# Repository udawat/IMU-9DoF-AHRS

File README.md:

IMU-9DoF-AHRS
=============

Explore Labs' 9 DoF IMU with Invensense's MPU-9150, Freescale Semiconductor's Pressure Sensor MPL3115A2 and Measurement Specialties' Humidity Sensor HTU21D and an optional GPS connector.

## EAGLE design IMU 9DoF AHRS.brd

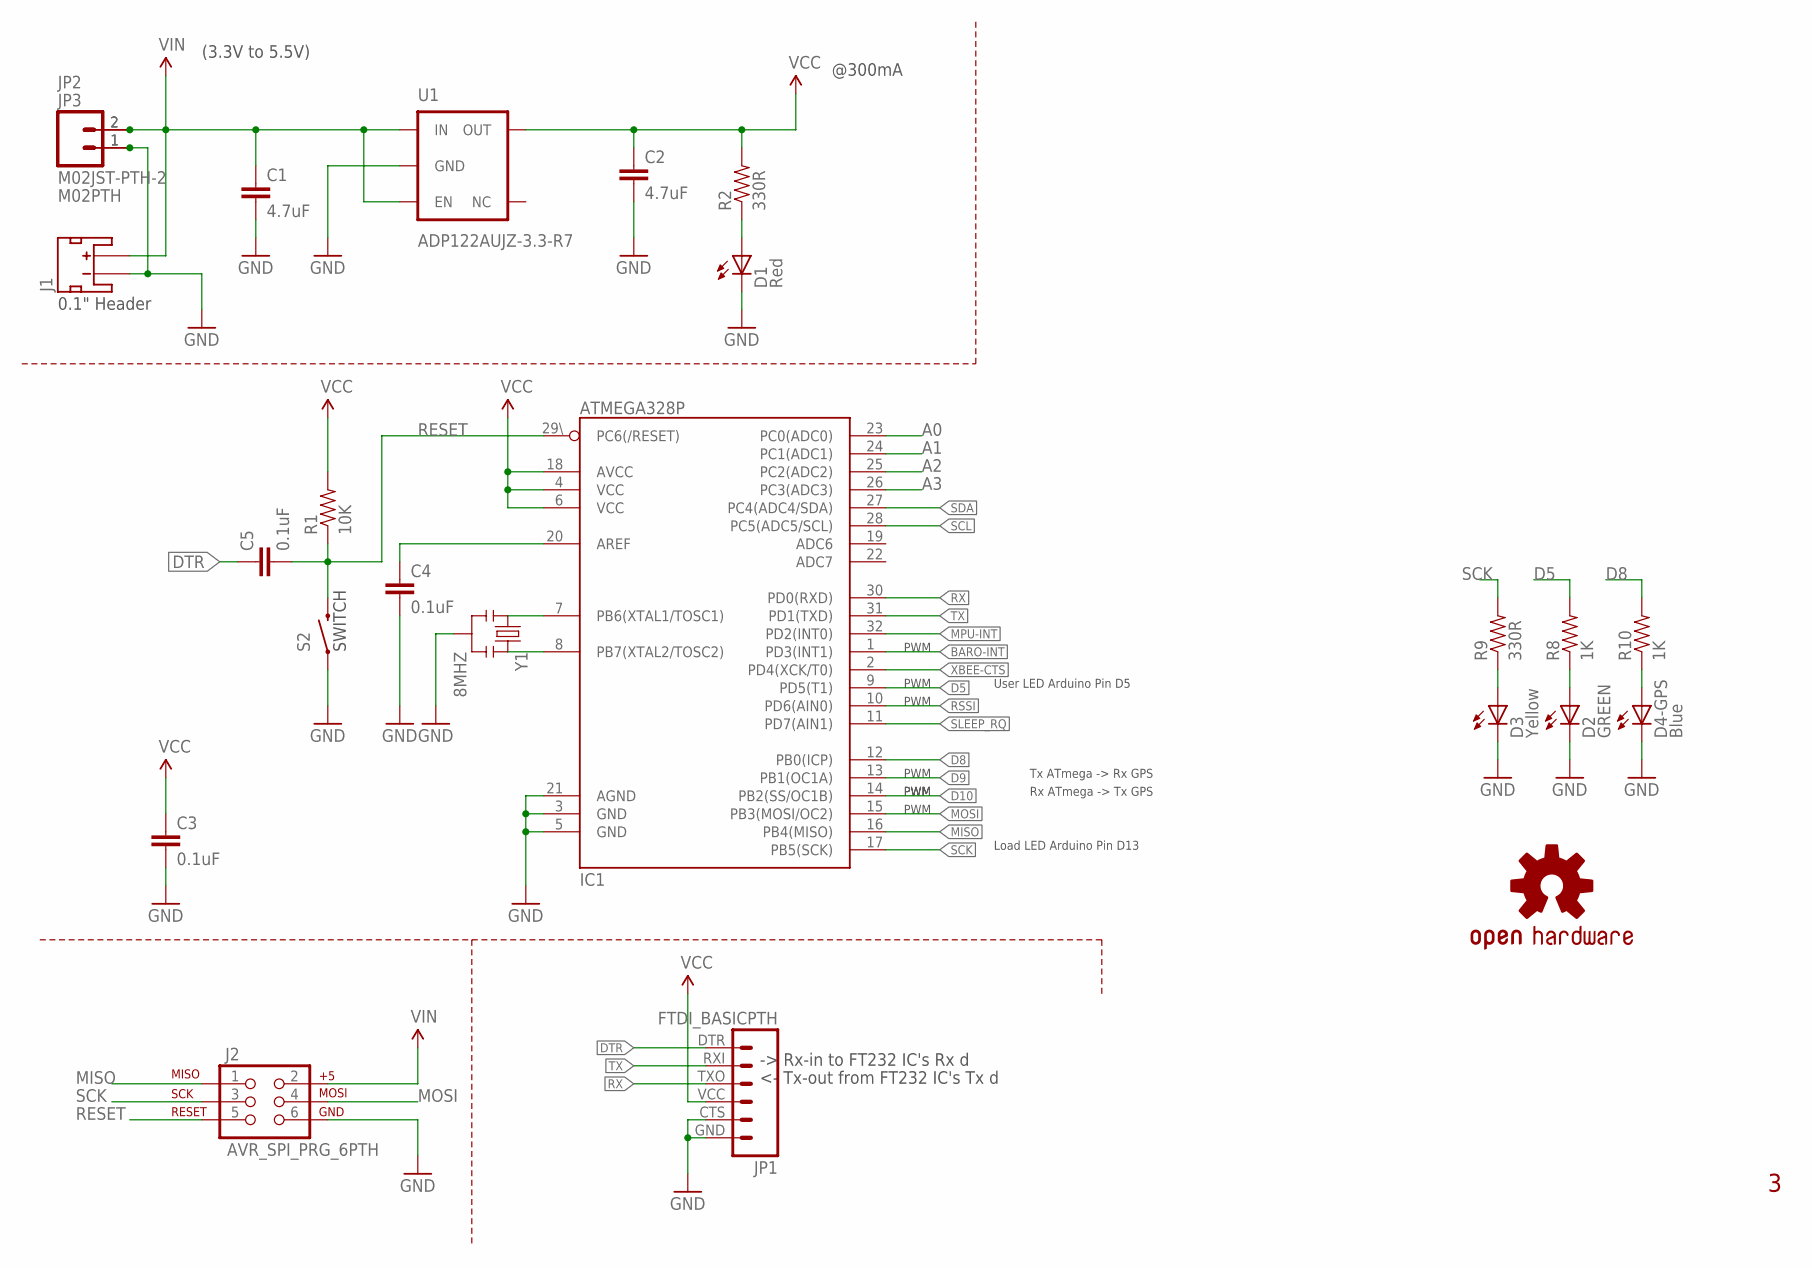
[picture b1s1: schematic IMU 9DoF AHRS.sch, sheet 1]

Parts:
C1, C2: 4.7uF; 0603-CAP
C3, C4, C5: 0.1uF; 0603-CAP
D1: Red; CHIPLED_0805
D2: GREEN; CHIPLED_0805
D3: Yellow; CHIPLED_0805
D4-GPS: Blue; CHIPLED_0805
IC1: ATMEGA328P; TQFP32-08
J1: JST_2MM_MALE; JST-2-SMD
J2: AVR_SPI_PRG_6PTH; 2X3
JP1: FTDI_BASICPTH; FTDI_BASIC
JP2: M02JST-PTH-2; JST-2-PTH
JP3: M02PTH; 1X02
LOGO4: OSHW-LOGOBOTTOM; OSHW-LOGO-M-BOTTOM
R1: 10K; 0603-RES
R2, R9: 330R; 0603-RES
R8, R10: 1K; 0603-RES
S2: SWITCH-MOMENTARY-2-SMD-1101NE; TACTILE-SWITCH-1101NE
U1: ADP122AUJZ-3.3-R7; SOT-23-5
Y1: 8MHZ; RESONATOR-SMD

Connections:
A0: IC1.23 (PC0(ADC0))
A1: IC1.24 (PC1(ADC1))
A2: IC1.25 (PC2(ADC2))
A3: IC1.26 (PC3(ADC3))
BARO-INT: IC1.1 (PD3(INT1)); also elsewhere on the board
D5: IC1.9 (PD5(T1)), R8.2
D8: IC1.12 (PB0(ICP)), R10.2; also elsewhere on the board
D9: IC1.13 (PB1(OC1A)); also elsewhere on the board
D10: IC1.14 (PB2(SS/OC1B)); also elsewhere on the board
DTR: C5.1, JP1.DTR (1)
GND: C1.2, C2.2, C3.2, C4.2, D1.C, D2.C, D3.C, D4-GPS.C, IC1.3 (GND), IC1.5 (GND), IC1.21 (AGND), J1.1 (-), J2.6, JP1.CTS (5), JP1.GND (6), JP2.1, JP3.1, S2.P$1 (1), U1.2 (GND), Y1.2; also elsewhere on the board
MISO: IC1.16 (PB4(MISO)), J2.1
MOSI: IC1.15 (PB3(MOSI/OC2)), J2.4
MPU-INT: IC1.32 (PD2(INT0)); also elsewhere on the board
unnamed: IC1.8 (PB7(XTAL2/TOSC2)), Y1.3
unnamed: IC1.7 (PB6(XTAL1/TOSC1)), Y1.1
unnamed: D3.A, R9.1
unnamed: C4.1, IC1.20 (AREF)
unnamed: D2.A, R8.1
unnamed: D1.A, R2.1
unnamed: D4-GPS.A, R10.1
RESET: C5.2, IC1.29\ (PC6(/RESET)), J2.5, R1.1, S2.P$2 (2)
RSSI: IC1.10 (PD6(AIN0)); also elsewhere on the board
RX: IC1.30 (PD0(RXD)), JP1.TXO (3); also elsewhere on the board
SCK: IC1.17 (PB5(SCK)), J2.3, R9.2
SCL: IC1.28 (PC5(ADC5/SCL)); also elsewhere on the board
SDA: IC1.27 (PC4(ADC4/SDA)); also elsewhere on the board
SLEEP_RQ: IC1.11 (PD7(AIN1)); also elsewhere on the board
TX: IC1.31 (PD1(TXD)), JP1.RXI (2); also elsewhere on the board
VCC: C2.1, C3.1, IC1.4 (VCC), IC1.6 (VCC), IC1.18 (AVCC), JP1.VCC (4), R1.2, R2.2, U1.5 (OUT); also elsewhere on the board
VIN: C1.1, J1.2 (+), J2.2, JP2.2, JP3.2, U1.1 (IN), U1.3 (EN); also elsewhere on the board
XBEE-CTS: IC1.2 (PD4(XCK/T0)); also elsewhere on the board

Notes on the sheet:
(3.3V to 5.5V)
@300mA
-> Rx-in to FT232 IC's Rx d
<- Tx-out from FT232 IC's Tx d
Load LED Arduino Pin D13
Tx ATmega -> Rx GPS
Rx ATmega -> Tx GPS
SWITCH
PWM
0.1" Header
User LED Arduino Pin D5

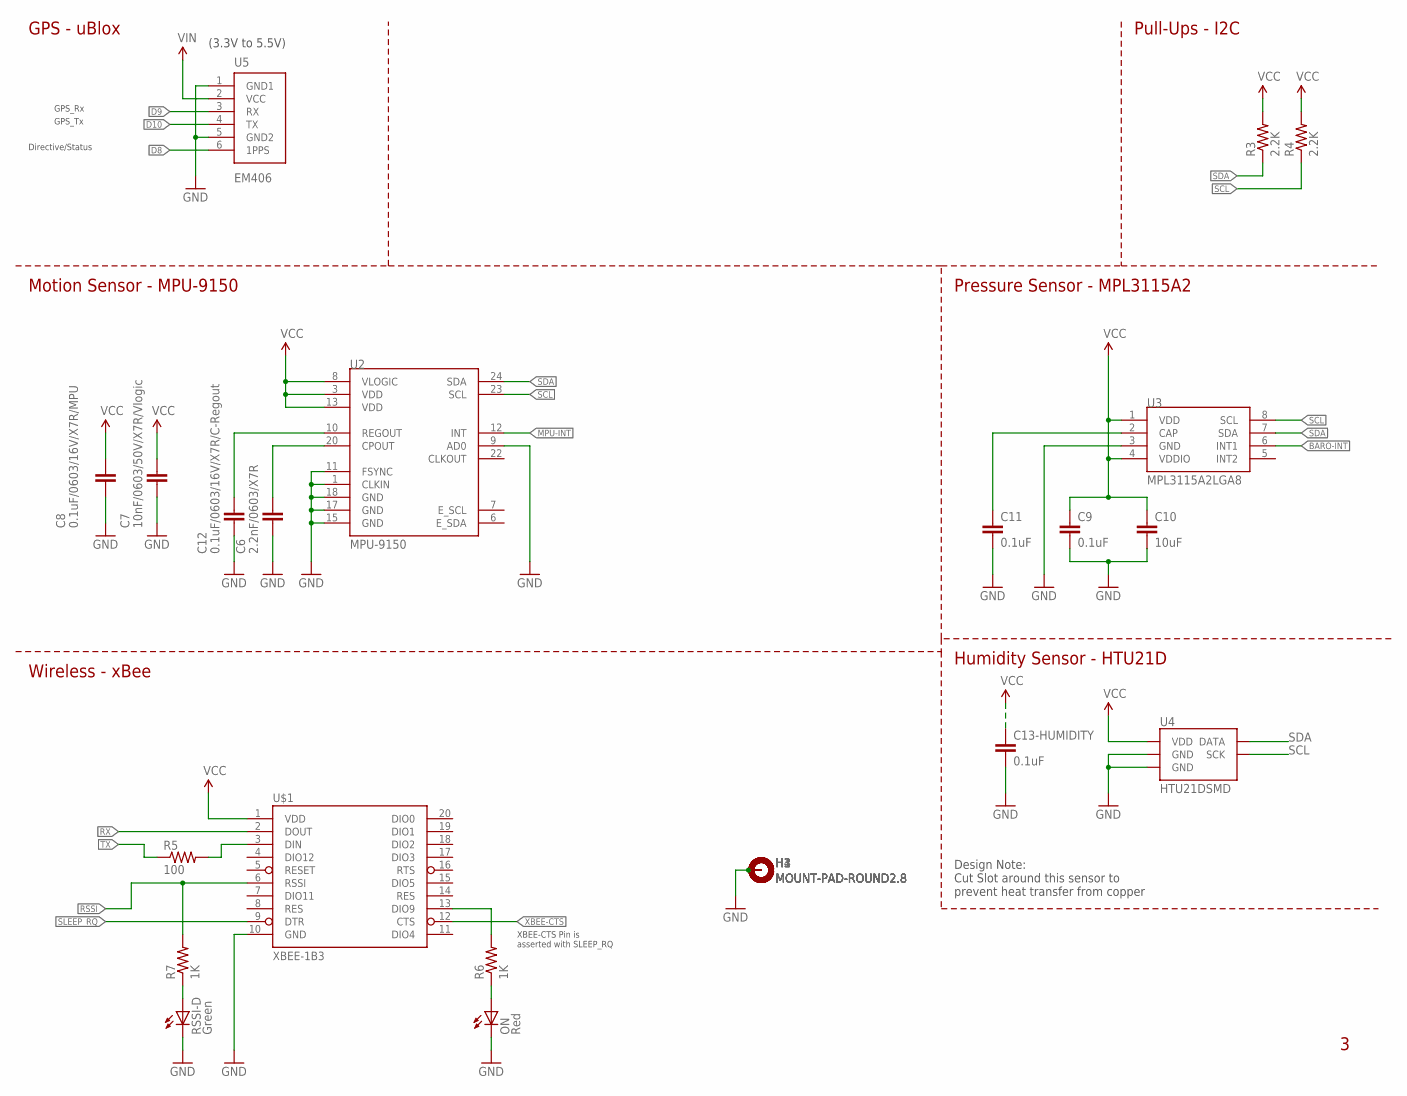
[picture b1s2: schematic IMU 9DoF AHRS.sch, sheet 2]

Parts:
C6: 2.2nF/0603/X7R; 0603-CAP
C7: 10nF/0603/50V/X7R/Vlogic; 0603-CAP
C8: 0.1uF/0603/16V/X7R/MPU; 0603-CAP
C9, C11, C13-HUMIDITY: 0.1uF; 0603-CAP
C10: 10uF; 0805
C12: 0.1uF/0603/16V/X7R/C-Regout; 0603-CAP
H1, H2, H3, H4: MOUNT-PAD-ROUND2.8; 2,8-PAD
ON: Red; CHIPLED_0805
R3, R4: 2.2K; 0603-RES
R5: 100; 0603-RES
R6, R7: 1K; 0603-RES
RSSI-D: Green; CHIPLED_0805
U2: MPU-9150QFN-24-NP; QFN-24-NP
U3: MPL3115A2LGA8; LGA8
U4: HTU21DSMD; HTU21D
U5: EM406
U$1: XBEE-1B3; XBEE-SMD

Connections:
BARO-INT: U3.6 (INT1); also elsewhere on the board
D8: U5.6 (1PPS); also elsewhere on the board
D9: U5.3 (RX); also elsewhere on the board
D10: U5.4 (TX); also elsewhere on the board
GND: C6.2, C7.2, C8.2, C9.2, C10.2, C11.2, C12.2, C13-HUMIDITY.2, H1.B2,8, H2.B2,8, H3.B2,8, H4.B2,8, ON.C, RSSI-D.C, U2.1 (CLKIN), U2.9 (AD0), U2.11 (FSYNC), U2.15 (GND), U2.17 (GND), U2.18 (GND), U3.3 (GND), U4.7 (GND), U4.GND, U5.1 (GND1), U5.5 (GND2), U$1.10 (GND); also elsewhere on the board
MPU-INT: U2.12 (INT); also elsewhere on the board
unnamed: C6.1, U2.20 (CPOUT)
unnamed: R5.2, U$1.3 (DIN)
unnamed: R7.1, RSSI-D.A
unnamed: R6.2, U$1.13 (DIO9)
unnamed: C12.1, U2.10 (REGOUT)
unnamed: ON.A, R6.1
unnamed: C11.1, U3.2 (CAP)
RSSI: R7.2, U$1.6 (RSSI); also elsewhere on the board
RX: U$1.2 (DOUT); also elsewhere on the board
SCL: R4.1, U2.23 (SCL), U3.8 (SCL), U4.SCK; also elsewhere on the board
SDA: R3.1, U2.24 (SDA), U3.7 (SDA), U4.DATA; also elsewhere on the board
SLEEP_RQ: U$1.9 (DTR); also elsewhere on the board
TX: R5.1; also elsewhere on the board
VCC: C7.1, C8.1, C9.1, C10.1, C13-HUMIDITY.1, R3.2, R4.2, U2.3 (VDD), U2.8 (VLOGIC), U2.13 (VDD), U3.1 (VDD), U3.4 (VDDIO), U4.VDD, U$1.1 (VDD); also elsewhere on the board
VIN: U5.2 (VCC); also elsewhere on the board
XBEE-CTS: U$1.12 (CTS); also elsewhere on the board

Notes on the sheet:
XBEE-CTS Pin is asserted with SLEEP_RQ
MPU-9150
Humidity Sensor - HTU21D
Pressure Sensor - MPL3115A2
Pull-Ups - I2C
Wireless - xBee
GPS_Rx
GPS_Tx
Directive/Status
Design Note: Cut Slot around this sensor to prevent heat transfer from copper
(3.3V to 5.5V)
GPS - uBlox
Motion Sensor - MPU-9150

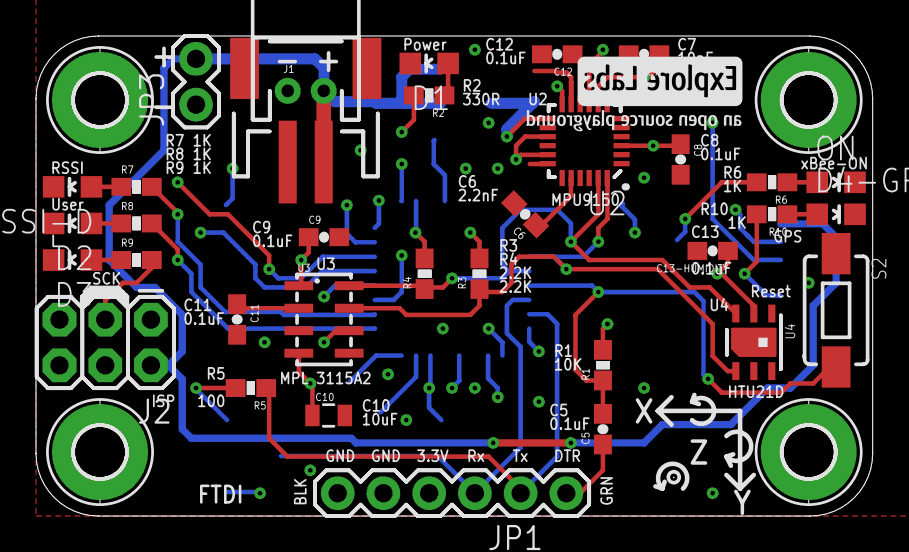
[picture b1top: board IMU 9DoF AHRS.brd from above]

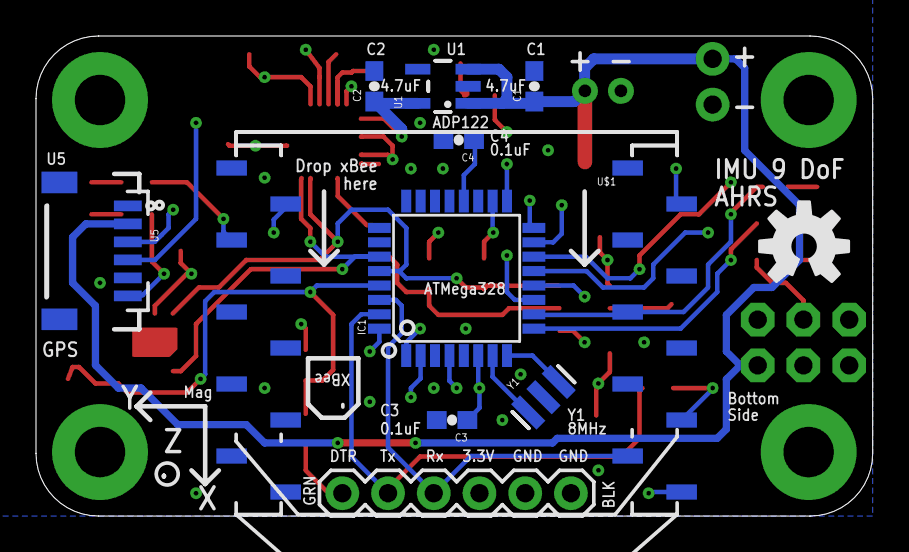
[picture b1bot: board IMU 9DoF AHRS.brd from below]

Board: 4 copper layers, 46.5 x 26.7 mm, 49 parts (10 on the bottom side), 35 nets.

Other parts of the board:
U$3: EXLABS_LOGO_0.25

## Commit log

2014-08-20 schematic in .pdf format and license update
2014-09-23 updated EAGLE files to latest revision
    updated EAGLE files to latest revision
    added Schematic in PDF format
    updated Gerber Data
2014-09-23 added supporting libraries
    Libraries for MPU9150, MPL3115A2 and HTU21D
2014-09-30 updated schematic pdf
    scale factor adjust
2014-11-24 Added firmware for the board.
    .ino file can be viewed or uploaded using Arduino IDE 1.0.6
2014-11-24 moving empty folders...
2014-11-25 tilt-compensated heading and userLED
    userLED now turn ON if Relative Humidity is above 50%
2015-12-22 Updated the MPU-9150 library with getMag function.
    Updated the MPU-6050 library with MPU-9150. Added getMag function in
    MPU-9150 library. Also, added I2Cdev library for single-source download.
2015-12-22 GPS LED fix
    The GPS LED on Pin 8 should not be defined as OUTPUT as the GPS module
    would loose its Fix.

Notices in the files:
parts and their libraries:
SparkFun-Passives: Licensing: CC v3.0 Share-Alike You are welcome to use this library for commercial purposes.
11xLabs: Released under the Creative Commons
11xLabs: http://creativecommons.org/licenses/by-sa/4.0
